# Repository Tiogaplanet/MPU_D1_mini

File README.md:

# MiP D1 mini pack
A [D1 mini](https://wiki.wemos.cc/products:d1:d1_mini) adapter board for [WowWee Labs'](https://github.com/WowWeeLabs/) [MiP](https://wowwee.com/mip) robot.  Similar to the [MiP ProMini Pack](https://github.com/adamgreen/MiP_ProMini-Pack), this board adapts the D1 mini and compatible boards to MiP.  Either install the D1 mini pack in a pair of pin headers or solder it directly to the board and you'll be programming MiP to connect to the Internet in no time.

## Acknowledgment
* As always, a big "thank you" goes out to [adamgreen](https://github.com/adamgreen/).  Without his help I'd still be wondering why my MiP won't talk to an Arduino.  Now, it's talking to the Internet!
* I'd also like to thank [Casey Kuhns](https://github.com/caseykuhns) who while at [SparkFun](https://github.com/sparkfun) developed the original [ProMini Pack](https://github.com/sparkfun/mip_promini-pack) and the [ProtoPack](https://github.com/sparkfun/mip_proto-pack) which provided the foundation for this project.

## OSH Park renderings

## Installation
Please see the [wiki](https://github.com/Tiogaplanet/MiP_D1-mini_pack/wiki) for up-to-date installation instructions.

## Disclaimer
I am a hobbyiest sharing this designed-at-home board with fans of robotics, MiP and the ESP8266 wifi chip.  While I strive to make this board as useful and "right" as it can be, in no way shall I be responsible for any damage that may occur to your MiP or D1 mini either incidently or directly through the use of this board.  You use this board at your own risk.

If you are experienced in robotics or circuit design and spot something that can or should be improved, please review [CONTRIBUTING.md](https://github.com/Tiogaplanet/MiP_D1-mini_pack/blob/master/CONTRIBUTING.md) and submit a pull request.

## License
Shield: [![CC BY-SA 4.0][cc-by-sa-shield]][cc-by-sa]

This work is licensed under a
[Creative Commons Attribution-ShareAlike 4.0 International License][cc-by-sa].

[![CC BY-SA 4.0][cc-by-sa-image]][cc-by-sa]

[cc-by-sa]: http://creativecommons.org/licenses/by-sa/4.0/
[cc-by-sa-image]: https://licensebuttons.net/l/by-sa/4.0/88x31.png
[cc-by-sa-shield]: https://img.shields.io/badge/License-CC%20BY--SA%204.0-lightgrey.svg

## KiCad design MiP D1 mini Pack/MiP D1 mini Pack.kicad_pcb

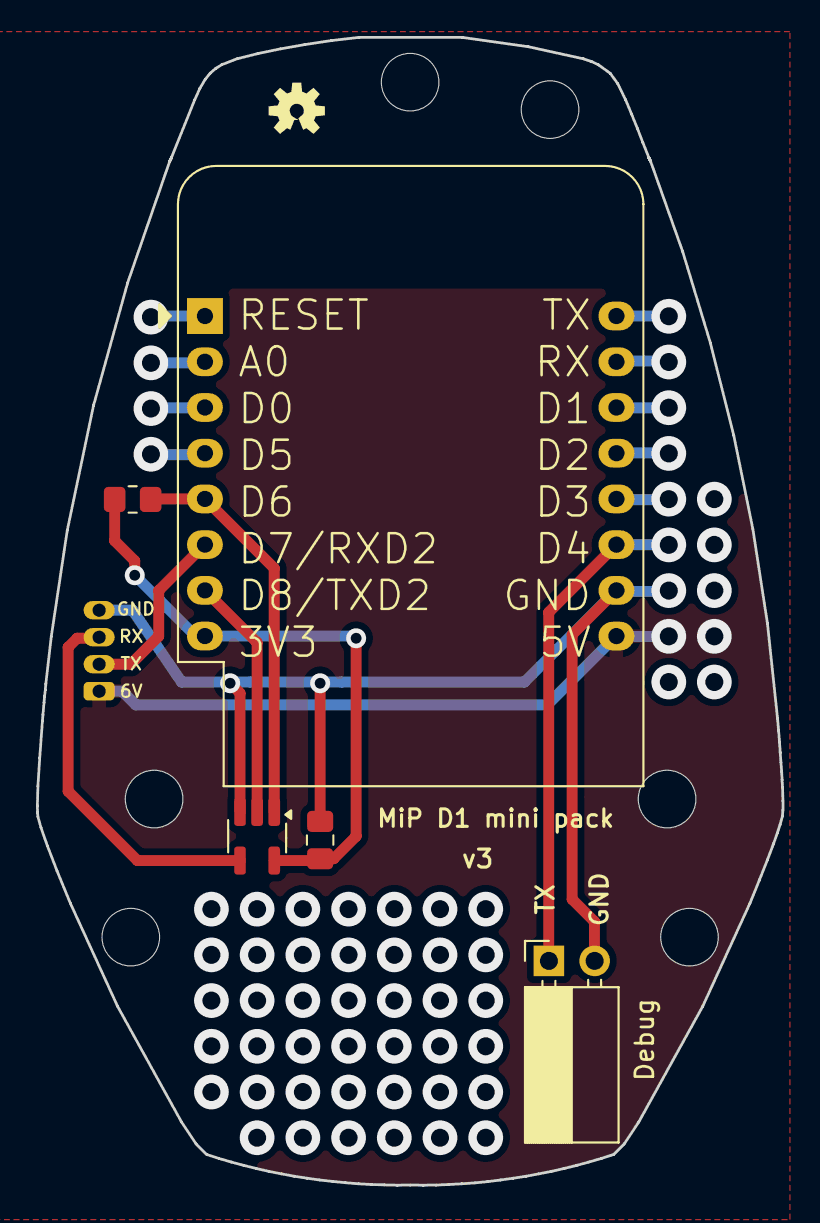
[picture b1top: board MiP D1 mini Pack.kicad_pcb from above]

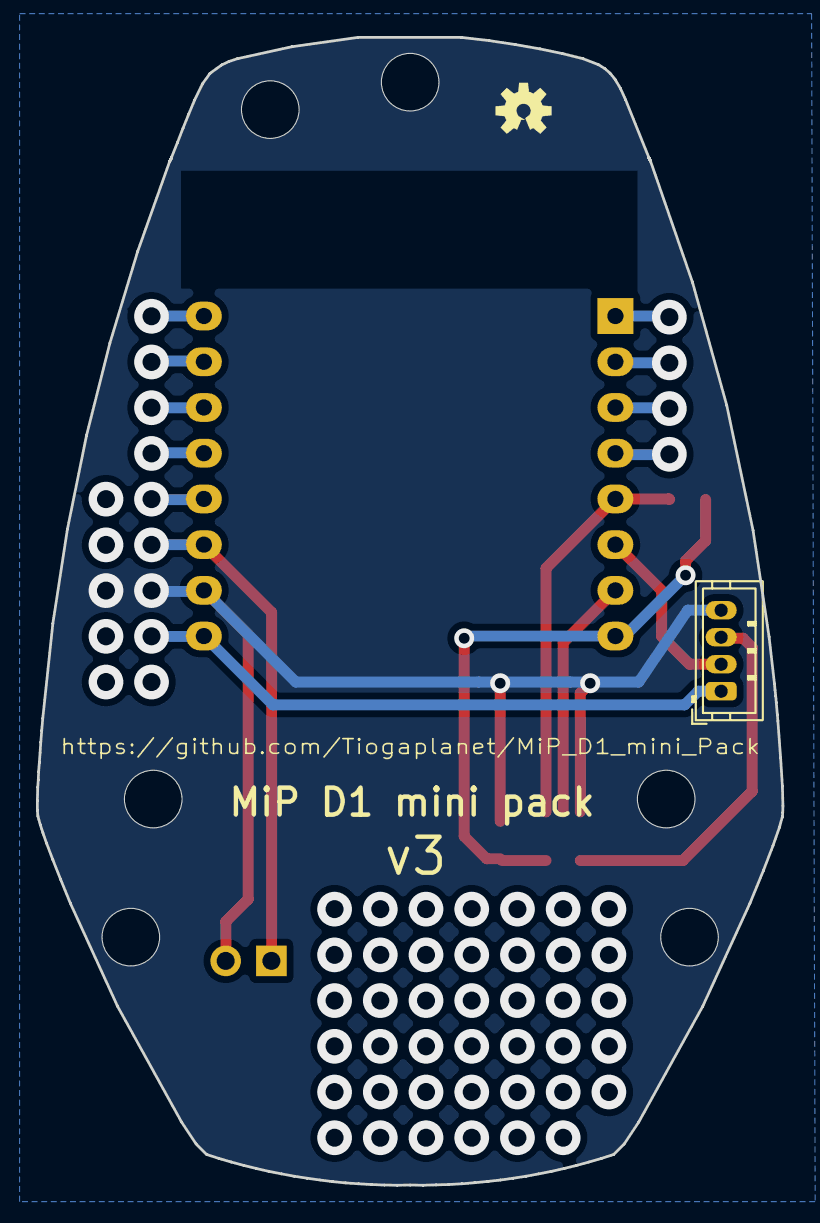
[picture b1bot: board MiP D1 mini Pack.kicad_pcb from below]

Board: 2 copper layers, 41.4 x 63.8 mm, 15 parts (2 on the bottom side), 7 nets.

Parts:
C1: .1μF; C_0805_2012Metric_Pad1.18x1.45mm_HandSolder
FRAME1: FRAME-LETTER; CREATIVE_COMMONS
J1: MiP; JST_ZH_B4B-ZR_1x04_P1.50mm_Vertical
J2: Debug; PinSocket_1x02_P2.54mm_Horizontal
LOGO2, LOGO2#2: OSHW-LOGOS; OSHW-LOGO-S
R1: 10K; R_0805_2012Metric_Pad1.20x1.40mm_HandSolder
U1: WEMOS D1 mini; WEMOS_D1_mini_light
U2: 74LVC1G125; SOT-23-5_HandSoldering
UNK_HOLE_0: dummyfp0
UNK_HOLE_1: dummyfp1
UNK_HOLE_2: dummyfp2
UNK_HOLE_3: dummyfp3
UNK_HOLE_4: dummyfp4
UNK_HOLE_5: dummyfp5

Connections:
+3V3: C1.1, R1.2, U1.8 (3V3), U2.5 (VCC_5)
+6V: J1.1, U1.9 (5V)
/BUF_TX: J1.3, U2.4
/D1_TX: U1.7 (CS/D8), U2.2
/Debug: J2.1 (Pin_1_1), U1.11 (D4)
/RX: J1.2, U1.6 (MOSI/D7)
unnamed: R1.1, U1.5 (MISO/D6), U2.1

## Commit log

2026-06-18 Update issue templates
    Added simple templates for bugs and feature requests
2026-06-19 Update README.md
    Pretty readme title
2026-06-20 Updated board images
    Updated the OSH Park renderings of the top and bottom of the board.
2026-06-20 Add a changelog
2026-06-20 Schematic cleanup
    Renamed the connector references to account for the lost J1 and J2 from the v2 board. Moved things around a bit.
2026-06-24 Updated pdf of schematic
2026-06-24 Remove title case
2026-06-24 More title case
    Not sure I even like calling it a "pack"
2026-06-24 Upload v3 board images
2026-06-24 Added BOM data to project file
    ignore xls files

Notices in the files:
parts and their libraries:
Released under the Creative Commons Attribution Share-Alike 4.0 License
https://creativecommons.org/licenses/by-sa/4.0
